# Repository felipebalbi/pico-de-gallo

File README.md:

# Pico de Gallo

A USB bridge that turns a [Raspberry Pi Pico 2](https://www.raspberrypi.com/products/raspberry-pi-pico-2/)
into a host-accessible I²C, SPI, UART, GPIO, PWM, ADC, and 1-Wire interface. Write and test
embedded Rust drivers on your development machine without cross-compiling
or flashing firmware to a target board.

## Overview

Pico de Gallo provides:

- **I²C**: read, write, write-then-read, bus scanning, and transaction batching
- **SPI**: read, write, full-duplex transfer, write-then-read, and transaction batching
- **UART**: read, write, flush, and baud rate configuration
- **GPIO**: digital input/output, edge event monitoring (subscribe/unsubscribe)
- **PWM**: 4-channel PWM output with configurable frequency and duty cycle
- **ADC**: 4 GPIO-based analog inputs (12-bit)
- **1-Wire**: bus reset, read, write, strong pullup, and ROM search (PIO hardware)
- **Configuration**: runtime I²C/SPI/UART/PWM frequency and SPI mode changes

All communication uses [postcard-rpc](https://docs.rs/postcard-rpc) over
USB — a compact, typed, binary RPC protocol.

## Book

The [Pico de Gallo Book](https://opendevicepartnership.github.io/pico-de-gallo/)
covers hardware assembly, firmware flashing, and a step-by-step guide to
writing an embedded device driver using Pico de Gallo.

## Crates

| Crate | Description |
|-------|-------------|
| [`pico-de-gallo-firmware`](crates/pico-de-gallo-firmware) | Embassy-rs firmware for the RP2350 |
| [`pico-de-gallo-lib`](crates/pico-de-gallo-lib) | Async host library (requires tokio) |
| [`pico-de-gallo-hal`](crates/pico-de-gallo-hal) | `embedded-hal` + `embedded-hal-async` implementation |
| [`pico-de-gallo-ffi`](crates/pico-de-gallo-ffi) | C FFI bindings (shared library + header) |
| [`gallo`](crates/pico-de-gallo-app) | CLI application for batch-mode access |
| [`pico-de-gallo-internal`](crates/pico-de-gallo-internal) | Shared wire-protocol types (internal) |

### Firmware

Embassy-rs firmware for the RP2350 that exposes I²C, SPI, UART, and GPIO
peripherals over USB via postcard-rpc endpoints.

### Library

Async host-side library wrapping the postcard-rpc transport. Provides
typed methods for every firmware endpoint. Requires the tokio runtime.

### HAL

Implements both `embedded-hal` and `embedded-hal-async` traits — including
`I2c`, `SpiBus`, `SpiDevice`, GPIO digital I/O, delay, and `embedded-io`
Read/Write for UART — so embedded device drivers written against those traits
can be tested on a host machine with real hardware attached to the Pico de Gallo.

### App

Command-line tool (`gallo`) for interactive and batch-mode I²C/SPI/UART/GPIO
access. Supports hex, binary, and ASCII output formats.

### FFI

C-compatible shared library wrapping the Rust host library. Generates a
C header via cbindgen. Suitable for integration into C/C++/Python/etc.
projects.

### Internal

Shared wire-protocol crate defining all postcard-rpc endpoints, request
and response types, and constants. Used by both firmware and host crates.

## Hardware

KiCAD schematic and PCB design for a Pico 2 daughter board. The v1.1
board features a single keyed 2x12 shrouded header that routes all 20
firmware signals with on-board I²C pull-ups and ADC input protection.

## Case

3D-printable snap-fit enclosure (FreeCAD) in two parts — body and lid.

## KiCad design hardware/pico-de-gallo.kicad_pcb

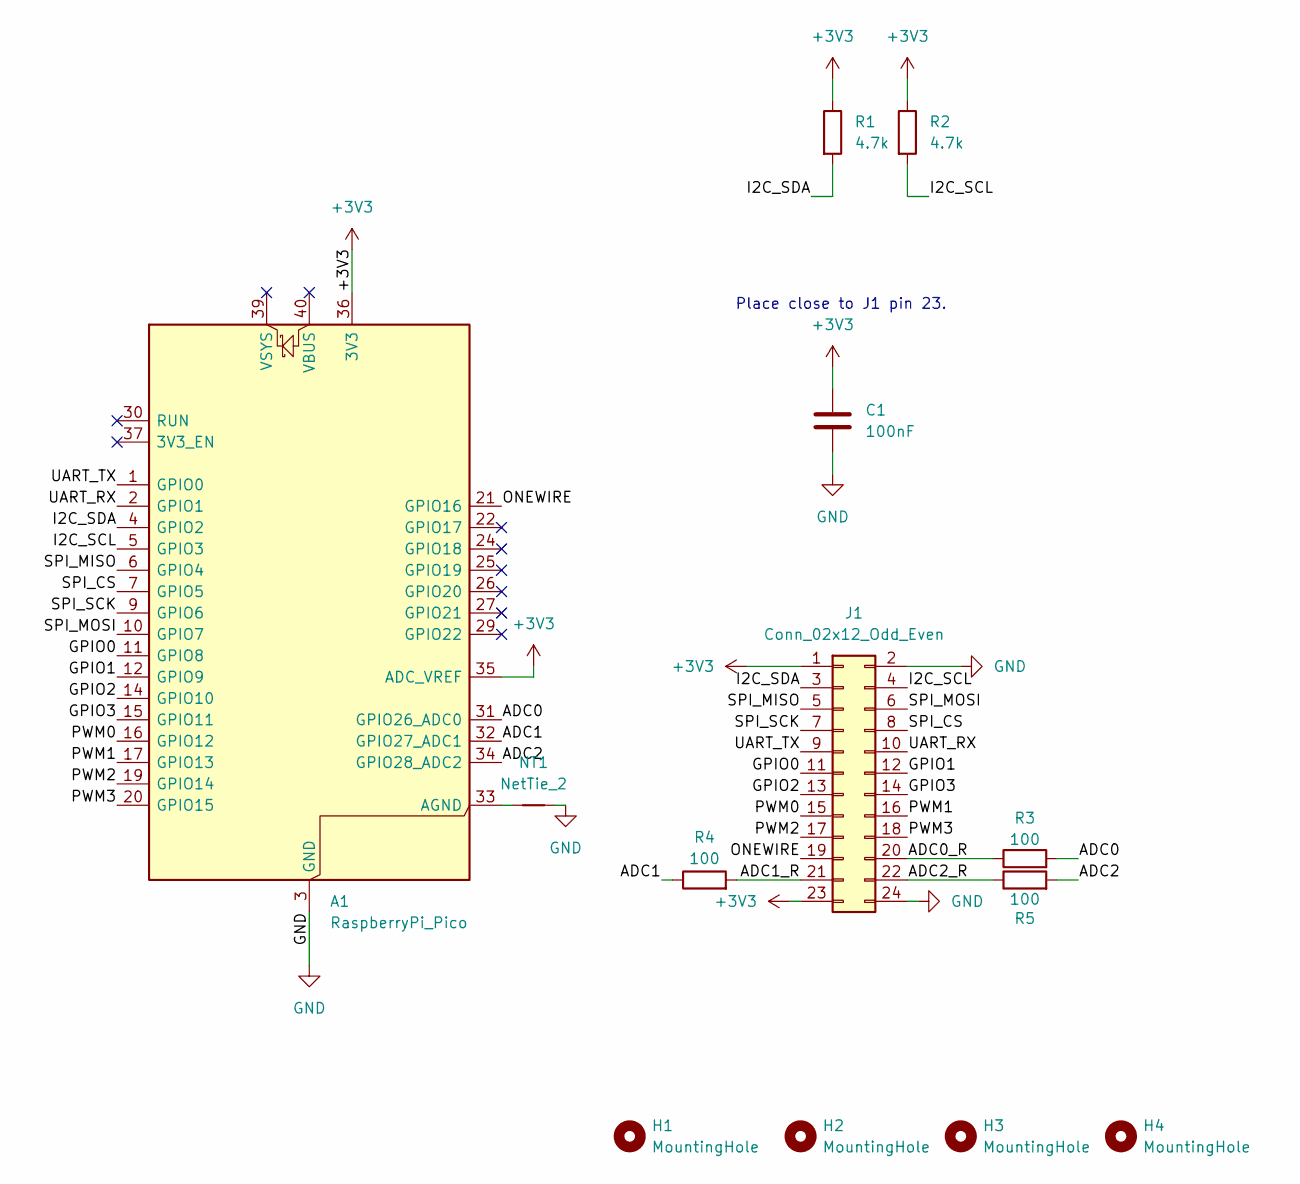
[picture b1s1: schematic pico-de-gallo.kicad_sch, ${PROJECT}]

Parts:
A1: RaspberryPi_Pico; RaspberryPi_Pico_Common_Unspecified; LCSC C41407547
C1: 100nF; C_0603_1608Metric_Pad1.08x0.95mm_HandSolder; LCSC C14663
H1, H2, H3, H4: MountingHole; MountingHole_3.2mm_M3
J1: Conn_02x12_Odd_Even; IDC-Header_2x12_P2.54mm_Vertical; LCSC C9137
NT1: NetTie_2; NetTie-2_SMD_Pad0.5mm
R1, R2: 4.7k; R_0603_1608Metric_Pad0.98x0.95mm_HandSolder; LCSC C23162
R3, R4, R5: 100; R_0603_1608Metric_Pad0.98x0.95mm_HandSolder; LCSC C22775

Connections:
+3V3: A1.35 (ADC_VREF), A1.36 (3V3), C1.1, J1.1, J1.23, R1.1, R2.1
/ADC0: A1.31 (GPIO26_ADC0), R3.2
/ADC0_R: J1.20, R3.1
/ADC1: A1.32 (GPIO27_ADC1), R4.1
/ADC1_R: J1.21, R4.2
/ADC2: A1.34 (GPIO28_ADC2), R5.2
/ADC2_R: J1.22, R5.1
/GPIO0: A1.11 (GPIO8), J1.11
/GPIO1: A1.12 (GPIO9), J1.12
/GPIO2: A1.14 (GPIO10), J1.13
/GPIO3: A1.15 (GPIO11), J1.14
/I2C_SCL: A1.5 (GPIO3), J1.4, R2.2
/I2C_SDA: A1.4 (GPIO2), J1.3, R1.2
/ONEWIRE: A1.21 (GPIO16), J1.19
/PWM0: A1.16 (GPIO12), J1.15
/PWM1: A1.17 (GPIO13), J1.16
/PWM2: A1.19 (GPIO14), J1.17
/PWM3: A1.20 (GPIO15), J1.18
/SPI_CS: A1.7 (GPIO5), J1.8
/SPI_MISO: A1.6 (GPIO4), J1.5
/SPI_MOSI: A1.10 (GPIO7), J1.6
/SPI_SCK: A1.9 (GPIO6), J1.7
/UART_RX: A1.2 (GPIO1), J1.10
/UART_TX: A1.1 (GPIO0), J1.9
GND: A1.3 (GND), A1.8 (GND), A1.13 (GND), A1.18 (GND), A1.23 (GND), A1.28 (GND), A1.38 (GND), C1.2, J1.2, J1.24, NT1.2
unnamed: A1.33 (AGND), NT1.1

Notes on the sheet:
Place close to J1 pin 23.

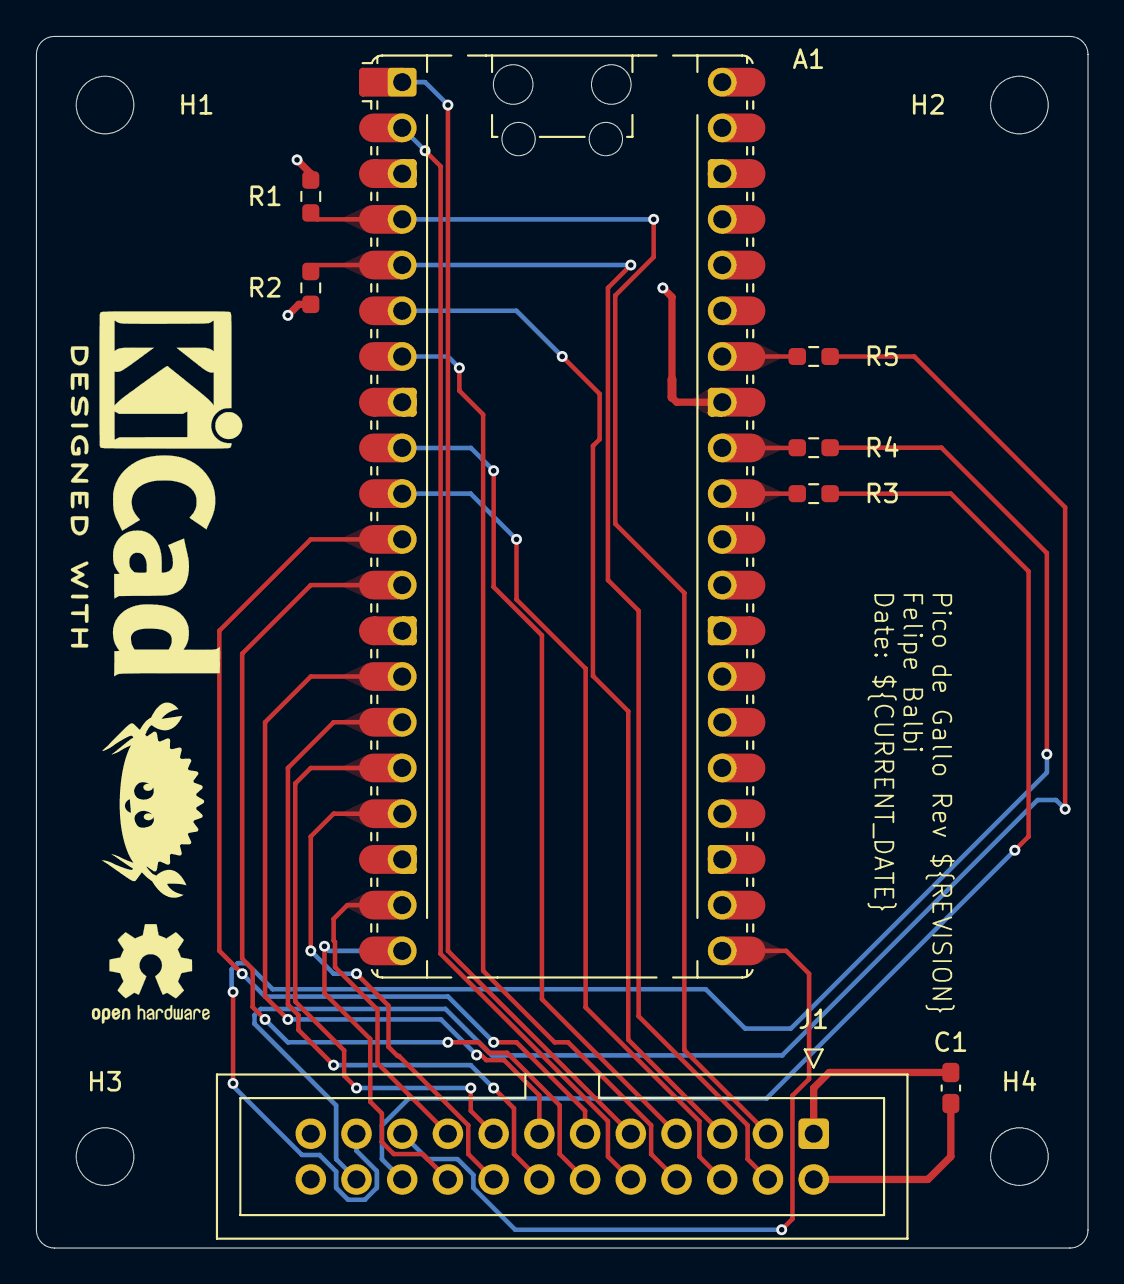
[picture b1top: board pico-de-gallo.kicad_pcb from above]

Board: 4 copper layers, 58.4 x 67.3 mm, 13 parts (0 on the bottom side), 26 nets.

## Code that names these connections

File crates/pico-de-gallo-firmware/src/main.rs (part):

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        Flex::new(p.PIN_11),
    ];

    // PWM on GPIO12-15 (slices 6-7)
    let pwm_config = pwm::Config::default();
    let pwm_slices = [
        Pwm::new_output_ab(p.PWM_SLICE6, p.PIN_12, p.PIN_13, pwm_config.clone()),
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    ];
    let pwm_configs = [pwm::Config::default(), pwm::Config::default()];

    // UART0 on GPIO0 (TX) and GPIO1 (RX) — default Pico 2 header pins
    #[cfg(feature = "hw-rev2")]
    let uart = {
        static UART_TX_BUF: StaticCell<[u8; 1024]> = StaticCell::new();
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        adc::Channel::new_pin(p.PIN_29, Pull::None),
    ];

    // 1-Wire — PIO0/SM0 on GPIO16
    #[cfg(feature = "hw-rev2")]
    let onewire = {
        let pio::Pio { mut common, sm0, .. } = pio::Pio::new(p.PIO0, Rev2Irqs);
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
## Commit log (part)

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2025-10-30 The Book
2025-11-05 Minor updates
2026-01-27 Make a new firmware release
2026-01-27 Update all other crates
2026-01-27 firmware: always use latest version
2026-01-28 Update README with Pico de Gallo book and API details
    Added a section about the Pico de Gallo book and updated API description.
2026-04-09 Publish pico de gallo book
2026-04-13 Correct gh-pages workflow
2026-04-20 Update clippy workflow
2026-04-20 Add gallo app tests
2026-04-20 Add more tests
2026-04-20 Update dependencies
    First update non-breaking changes.
2026-04-20 Update remaining dependencies
2026-04-20 pico-de-gallo-lib: bump to 0.2.1
2026-04-20 internal, lib, firmware: document and share MAX_TRANSFER_SIZE constant
    Extract the firmware's local BUFFER_SIZE (512) into a shared
    MAX_TRANSFER_SIZE constant in pico-de-gallo-internal so both firmware
    and host code reference the same source of truth.
    Update lib doc comments on i2c_read, i2c_write_read, and spi_read to
    warn callers about the 512-byte transfer limit.
2026-04-20 app, hal, lib, internal: usability improvements
    HAL:
    - Add Error::Message variant with descriptive string context
    - Implement Display and std::error::Error for Error
    - Implement StatefulOutputPin for Gpio (is_set_low/is_set_high)
    Lib:
    - Remove FlattenErr trait; inline .map_err(PicoDeGalloError::Endpoint)
2026-04-20 ffi: add compile-time Send + Sync assertion for thread safety
    The FFI handle is passed as a raw pointer to C code which may call
    functions from multiple threads concurrently. All FFI functions take
    only shared references to the inner PicoDeGallo, which is safe because
    HostClient is internally Arc-wrapped and Send + Sync.
    Add a const assertion that will produce a compile error if the inner
    type ever loses its Send + Sync bounds, preventing silent unsoundness.
2026-04-20 ci: fix Windows release asset naming
    The Windows release job was uploading the .dll with a .lib extension,
    making it unusable for both runtime loading and link-time binding.
    Upload both the .dll (runtime) and .dll.lib (import library) with
    correct file extensions so consumers can both link and load.
2026-04-20 docs: add comprehensive documentation across all crates
    Add crate-level, struct-level, and field-level rustdoc comments to
    all six crates. Update all README files and the book to reflect
    current features.
    Source documentation:
    - internal: crate-level docs with wire compatibility warning, feature
    flags guide, and organization overview. Document all constants,
2026-04-20 split set-config into i2c set-config and spi set-config
    Break the unified set-config command into separate I2C and SPI
    configuration commands across the entire stack. Replace the raw u32
    I2C frequency with a type-safe I2cFrequency enum (Standard/Fast/
    FastPlus) matching the I2C specification modes supported by the
    RP2350.
    Wire protocol (internal):
2026-04-20 chore: bump all crate versions for breaking changes
    internal: 0.2.1 → 0.3.0
    - Split SetConfigurationRequest into I2c/Spi variants
    - Added I2cFrequency enum replacing raw u32
    - Added SpiTransfer endpoint types
    - Added GpioState From<bool> conversions
    - Added MAX_TRANSFER_SIZE constant
2026-04-21 dos2unix CHANGELOG.md
2026-04-21 docs: fix MAX_TRANSFER_SIZE references in lib rustdoc
    The rustdoc comments on i2c_read, i2c_write_read, and spi_read
    incorrectly stated the firmware buffer limit as 512 bytes. The actual
    value of MAX_TRANSFER_SIZE is 4096 bytes, as defined in
    pico-de-gallo-internal.
    Update ROADMAP.md to mark item 1.6 complete.
    Closes #6
2026-04-21 feat!: replace unit-struct errors with rich error enums (#1)
    BREAKING CHANGE: wire protocol is not backward compatible — firmware
    and host crates must be upgraded together.
    Replace 12 unit-struct error types (I2cReadFail, SpiWriteFail, etc.)
    with 3 rich error enums that propagate real hardware error details:
    - I2cError: NoAcknowledge, ArbitrationLoss, Bus, Overrun,
    BufferTooLong, AddressOutOfRange, Other
2026-04-21 i2c: add bus scan endpoint returning address list
    Add a dedicated `i2c/scan` endpoint that probes all 7-bit I2C addresses
    in a single USB round-trip, replacing the previous approach of 112
    individual `i2c_read` calls from the host.
    The firmware handler attempts a 1-byte read at each address and collects
    those that ACK into a `Vec<u8>` (host) / `&[u8]` (firmware) of
    responding addresses. An `include_reserved` flag controls whether
2026-04-21 feat(gpio): add runtime direction and pull-resistor configuration (#4)
    Add gpio/set-config endpoint for runtime GPIO pin direction (input/output)
    and pull-resistor (none/up/down) configuration. Once a pin is configured,
    it enters explicit mode — get/wait on output pins or put on input pins
    returns the new WrongDirection error. Unconfigured pins retain backward-
    compatible auto-switching behavior.
    Closes #4
2026-04-21 feat: add i2c/get-config and spi/get-config query endpoints
    Add configuration query endpoints that return the active bus settings
    without relying on host-side state tracking.
    Internal:
    - I2cGetConfiguration and SpiGetConfiguration endpoints
    - SpiConfigurationInfo struct (frequency, phase, polarity)
    - I2cGetConfigurationResponse and SpiGetConfigurationResponse type aliases
2026-04-21 Fix gpio direction and pull tests
2026-04-21 feat: add PWM support (4 channels on GPIO 12–15)
    Add 4-channel PWM output using RP2350 PWM slices 6–7 (GPIO 12–15).
    This is a breaking change: GPIO count is reduced from 8 to 4 (GPIO 8–11)
    to free pins for PWM.
    internal:
    - 6 new endpoints: pwm/set-duty-cycle, pwm/get-duty-cycle, pwm/enable,
    pwm/disable, pwm/set-config, pwm/get-config
2026-04-21 internal: some tests require use-std
2026-04-21 feat: add GPIO event topics (subscribe/unsubscribe edge monitoring)
    Implement push-based GPIO edge notifications using postcard-rpc topics.
    A host can subscribe to a GPIO pin for rising, falling, or any edge
    events. The firmware transfers pin ownership to a pooled monitor task,
    publishes GpioEvent messages (pin, edge, timestamp_us) over the
    GpioEventTopic, and returns the pin on unsubscribe. While monitored,
    gpio_get/put/wait/set_config returns GpioError::PinMonitored.
2026-04-22 feat: add I2C/SPI transaction batching across all crates
    Implement batch endpoints that pack multiple I2C or SPI operations into
    a single USB transfer, reducing round-trips from N to 1 for
    multi-operation transactions (10-50× speedup).
    Wire format uses a flat packed byte stream — postcard cannot zero-copy
    borrow enum slices on no_std, so operations are encoded as:
    I2C: 0x00+u16BE(len) = Read, 0x01+u16BE(len)+data = Write
2026-04-22 Minor cleanup
2026-04-22 chore: remove ADC temperature sensor support
    Remove the RP2350 on-die temperature sensor endpoint and all
    references. Exposing GPIO-based ADC channels:(ADC0–ADC3) remains; only
    the internal die temperature sensor is removed as it provides no
    practical value for a USB bridge.
    Changes across all 6 crates + docs:
    - internal: Remove AdcReadTemperatureResponse type alias,
2026-04-22 feat: add logic capture, 1-Wire, batched transactions, and ADC improvements
    Logic Capture (issue #16):
    - internal: CaptureStart/CaptureStop endpoints, CaptureDataTopic (device-
    to-host streaming), CaptureError enum (6 variants), CaptureStartRequest,
    CaptureStartInfo, CaptureStopInfo, CaptureData types. Constants:
    CAPTURE_CHANNEL_MIN/MAX (0/3), MAX_CAPTURE_CHANNELS (4),
    CAPTURE_MIN/MAX_SAMPLE_RATE_HZ.
2026-04-22 Defer 3.5 and 3.6 to post-v1.0
2026-04-22 Remove logic capture feature, defer to future milestone
    The logic capture feature (PIO-based digital sampling, analyzer TUI,
    protocol decoding) isn't ready to reliably deliver data from firmware
    to host. Remove it entirely and defer to a future milestone.
2026-04-22 Mark std-only tests
    Some tests rely on Vec and, as such, should only one on use-std builds.
2026-04-23 Pico de Gallo Hardware v1.1
    Update the PCB for revision 1.1 of the main board.
2026-04-23 Update to latest kicad-actions
2026-04-23 docs: document v1.1 landing board and v1.0 best-effort notice
    Add the v1.1 2x12 header pinout (24 pins, all 20 firmware signals) to
    the Getting Started chapter. Pin 1 (VREF) is at the top-right when the
    board is held with USB facing up; the shroud key faces right.
    Mark v1.0 as best-effort: UART, SPI CS, 1-Wire, and ADC are not routed
    on the original board.
    Update Pin Map: add SPI CS (GPIO 5), drop broken ADC3, change
2026-04-23 firmware: split main.rs into context and handler submodules
    No functional changes, resulting binary is identical.
2026-04-23 Better names
2026-04-27 Add python bindings
    Closes #30
2026-04-27 pyco: macos only for aarch64
2026-04-27 Update to latest actions versions
2026-04-27 Add a slightly more complex python example
2026-04-27 Add examples for the rest of the existing APIs
2026-05-04 dos2unix
2026-05-06 Update LICENSE copyright and add AI attribution instructions
2026-05-11 chore(deps)(deps): bump tokio from 1.52.2 to 1.52.3 in /crates
    Bumps [tokio](https://github.com/tokio-rs/tokio) from 1.52.2 to 1.52.3.
    - [Release notes](https://github.com/tokio-rs/tokio/releases)
    - [Commits](https://github.com/tokio-rs/tokio/compare/tokio-1.52.2...tokio-1.52.3)
    ---
    updated-dependencies:
    - dependency-name: tokio
2026-05-18 Update kicad project
2026-05-18 Move v1.0 case to subdirectory
2026-05-18 Add v1.1 case
2026-05-30 Revert "chore(main): release internal 1.0.0"
    This reverts commit c5487f43f21c978517b617966f7b091ecc682afa.
2026-06-01 chore(deps)(deps): bump tabled from 0.20.0 to 0.21.0 in /crates
    Bumps [tabled](https://github.com/zhiburt/tabled) from 0.20.0 to 0.21.0.
    - [Changelog](https://github.com/zhiburt/tabled/blob/master/CHANGELOG.md)
    - [Commits](https://github.com/zhiburt/tabled/commits)
    ---
    updated-dependencies:
    - dependency-name: tabled
2026-06-09 chore(ci)(deps): bump actions/checkout from 4 to 6
    Bumps [actions/checkout](https://github.com/actions/checkout) from 4 to 6.
    - [Release notes](https://github.com/actions/checkout/releases)
    - [Changelog](https://github.com/actions/checkout/blob/main/CHANGELOG.md)
    - [Commits](https://github.com/actions/checkout/compare/v4...v6)
    ---
    updated-dependencies:
2026-06-09 chore(ci)(deps): bump actions/upload-artifact from 4 to 7
    Bumps [actions/upload-artifact](https://github.com/actions/upload-artifact) from 4 to 7.
    - [Release notes](https://github.com/actions/upload-artifact/releases)
    - [Commits](https://github.com/actions/upload-artifact/compare/v4...v7)
    ---
    updated-dependencies:
    - dependency-name: actions/upload-artifact
2026-06-09 chore(main): release ffi 0.7.0
2026-06-09 chore(main): release firmware 0.10.0
2026-06-09 chore(main): release library 0.6.0
2026-06-09 chore(main): release internal 0.6.0
2026-06-09 chore(main): release hal 0.6.0
2026-06-09 chore(main): release pyco 0.3.0
2026-06-09 chore(main): release application 0.7.0
2026-06-12 Update PCB/PRO
2026-06-12 add Pico2 LCSC part number
2026-06-12 chore(main): release pico-de-gallo libraries
2026-06-18 Fix JLCPCB part number
2026-06-22 chore(ci)(deps): bump actions/checkout from 6 to 7
    Bumps [actions/checkout](https://github.com/actions/checkout) from 6 to 7.
    - [Release notes](https://github.com/actions/checkout/releases)
    - [Changelog](https://github.com/actions/checkout/blob/main/CHANGELOG.md)
    - [Commits](https://github.com/actions/checkout/compare/v6...v7)
    ---
    updated-dependencies:
2026-06-22 chore(pyco): fix wheel version in pyproject.toml
2026-06-22 chore(pyco): link readme on pyproject.toml

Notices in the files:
hardware/pico-de-gallo.kicad_pcb:
https://creativecommons.org/licenses/by-sa/4.0
Released under the Creative Commons
